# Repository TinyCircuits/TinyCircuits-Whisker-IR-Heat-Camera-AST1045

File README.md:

# TinyCircuits-Wireling-IR-Heat-Camera-AST1045
# Rev 1

The design files are located under design_files/ for the TinyCircuits AST1045 Rev 1 PCB. This is a Wireling board which features an IR thermal Camera using the AMG8833 IR Array Gird-EYE Sensor.
Format is in Cadsoft Eagle format - Eagle version 6.2 was used for the original design.

For more infomation on this, check out the product page at TinyCircuits.com

# License:

Design by TinyCircuits.
All design files are released under the Creative Commons Attribution Share-Alike 3.0 License, see the following link for details: http://creativecommons.org/licenses/by-sa/3.0

All text above must be included in any redistribution or derived design

This project uses designs and concepts developed as part of the Arduino project and the LilyPad project.  The TinyCircuits design files themselves (schematics, PCB and libraries) are not directly derived from these works' design files and have been created new, however the concepts and basic architecture behind the TinyDuino and TinyLily products are derived and we thank the hard work of the organizations below for their contributions to open-source hardware:
  
Original Arduino Uno Design by Team Arduino

LilyPad Arduino Design by Leah Buechley and Sparkfun Electronics

Please support the open-source hardware community

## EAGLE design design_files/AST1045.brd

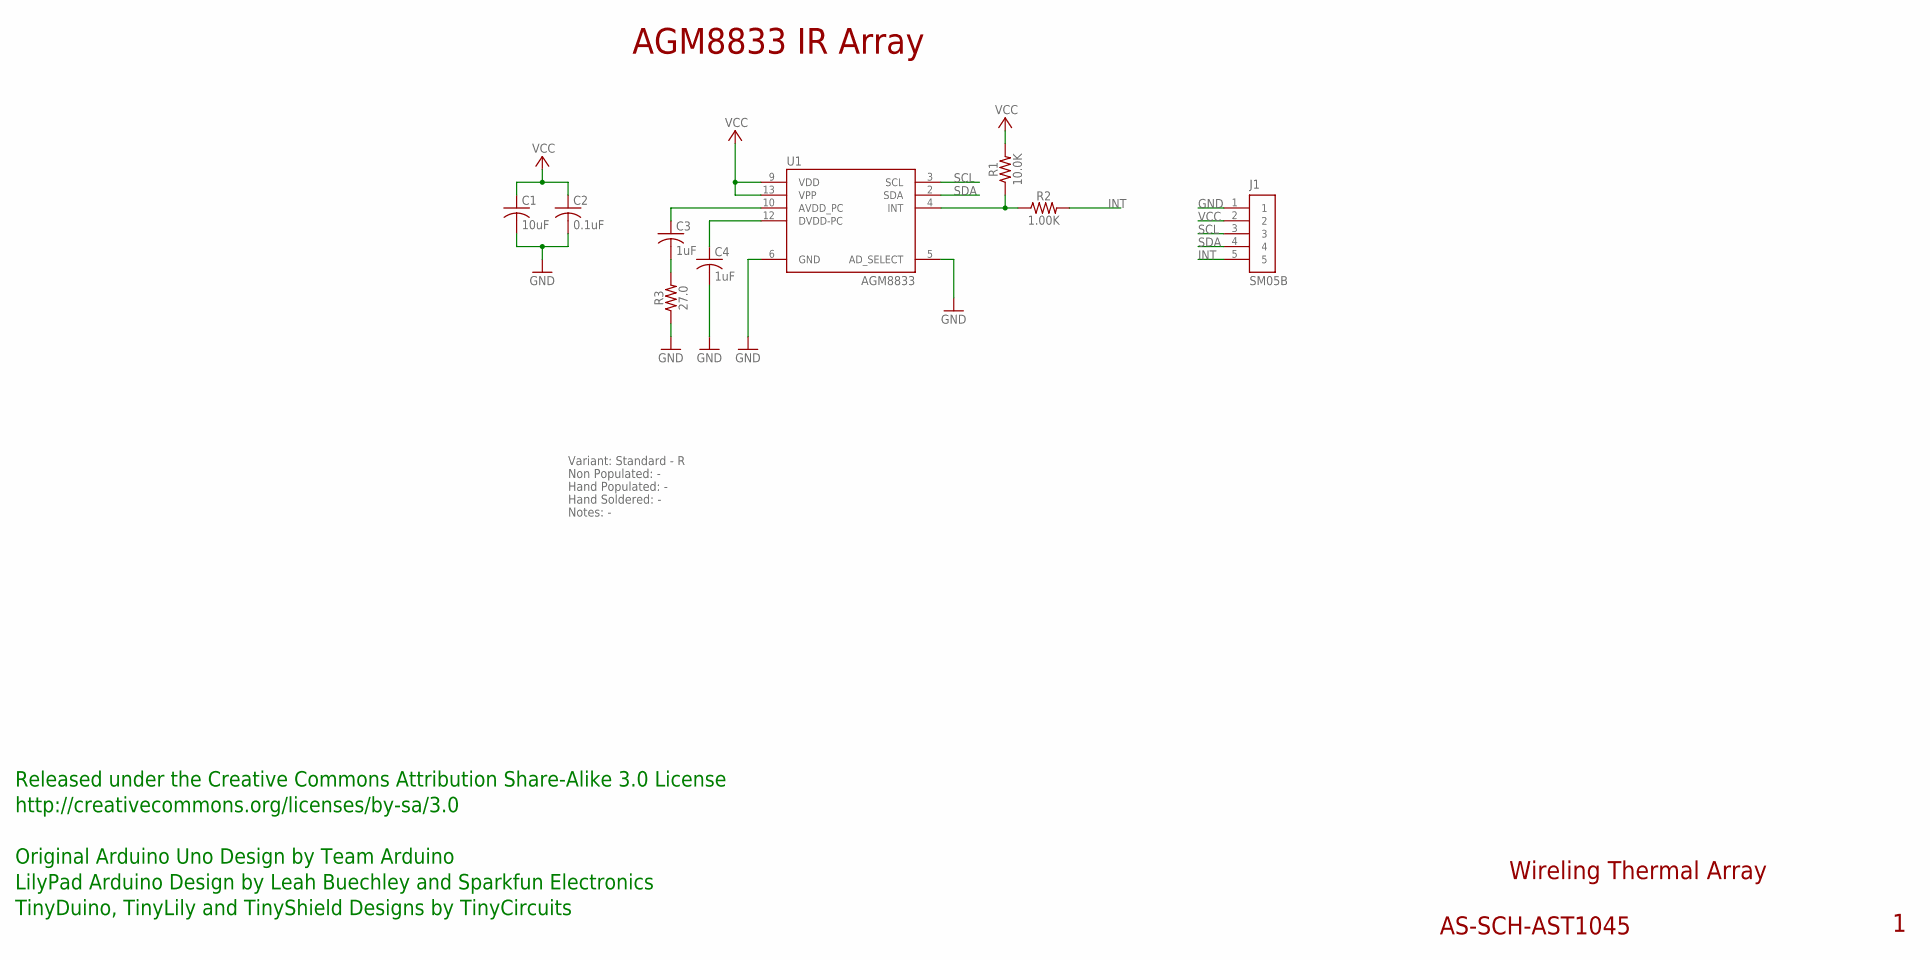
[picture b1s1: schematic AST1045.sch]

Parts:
C1: 10uF; C0603
C2: 0.1uF; C0402
C3: 1uF; C0402
C4: 1uF; C0402; PARTNO AS-ITM-00105
J1: SM05B; JST_SH_5X1
R1: 10.0K; 0402; PARTNO AS-ITM-00032
R2: 1.00K; 0402; PARTNO AS-ITM-00003
R3: 27.0; 0402
U1: AGM8833; AMG8833

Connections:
GND: C1.2, C2.2, C4.2, J1.1, R3.1, U1.5 (AD_SELECT), U1.6 (GND)
INT: J1.5, R2.2
unnamed: C3.1, U1.10 (AVDD_PC)
unnamed: C3.2, R3.2
unnamed: C4.1, U1.12 (DVDD-PC)
unnamed: R1.1, R2.1, U1.4 (INT)
SCL: J1.3, U1.3 (SCL)
SDA: J1.4, U1.2 (SDA)
VCC: C1.1, C2.1, J1.2, R1.2, U1.9 (VDD), U1.13 (VPP)

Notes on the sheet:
Wireling Thermal Array
AS-SCH-AST1045
AGM8833 IR Array
Released under the Creative Commons Attribution Share-Alike 3.0 License
http://creativecommons.org/licenses/by-sa/3.0
Original Arduino Uno Design by Team Arduino
TinyDuino, TinyLily and TinyShield Designs by TinyCircuits
LilyPad Arduino Design by Leah Buechley and Sparkfun Electronics
Non Populated: -
Hand Populated: -
Hand Soldered: -
Variant: Standard - R
Notes: -

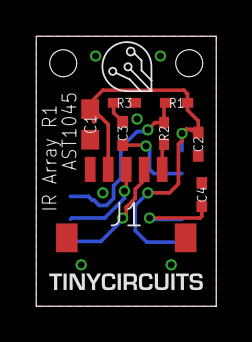
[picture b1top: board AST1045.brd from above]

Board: 2 copper layers, 10.0 x 15.0 mm, 10 parts (1 on the bottom side), 9 nets.

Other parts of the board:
U$1: DOCFIELD-TINYCIRCUITS-PCB

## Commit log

2019-09-23 datasheet
2019-12-17 updated documentation
2020-01-16 images
2020-01-17 library
2020-01-17 code
2020-02-04 mass image update
2020-02-04 added example
2020-08-14 Add CAD data
